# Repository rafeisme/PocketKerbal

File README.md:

# PocketKerbal
Kerbal Space Program Controller using PocketBeagle

(Soon to be) Home to KerbalController!

This is a personalized Kerbal Space Program console built using a PocketBeagle and kRPC. 

More information can be found on my Hackster Page: https://www.hackster.io/rfn1/pocketkerbal-ksp-console-using-pocketbeagle-krpc-d380ad 

The program you need to use/edit is called Project_1_v2
It is actually intiated using a run program. 
For these files, see https://github.com/rafeisme/ENGI301

Currently this repository houses the PCB files for PocketKerbal. These still need some work, but should be functional. The board is the same size as the actual console, and is designed to be fitted behind it. For the sake of simplicity, some of the unique buttons and switches have been temporarily swapped out for generic ones. 
In total there are:
15 toggle switches
4 buttons
20 resistors
2 joysticks
2 potentiometers
2 led bars
2 leds
1 sliding potentiometer
1 display

A more comprehensive parts list can be found on the Hackster Page. 

NOTE: The "PocketBeagle Device" had not been made when the PCB layout was done, so the example PocketBeagle is included here. The file for the custom PocketBeagle is included in the library.
NOTE: The project guidelines mentioned a 4"x5" maximum size, but in order to fit all of the components and be the size of the console, PocketKerbal is 12" x 6". It could be reduced if it was necessary. 
NOTE: The LCD screen was used as opposed to the SPI screen in my library. https://www.adafruit.com/product/181 

This is still a work in progress and will be updated soon.

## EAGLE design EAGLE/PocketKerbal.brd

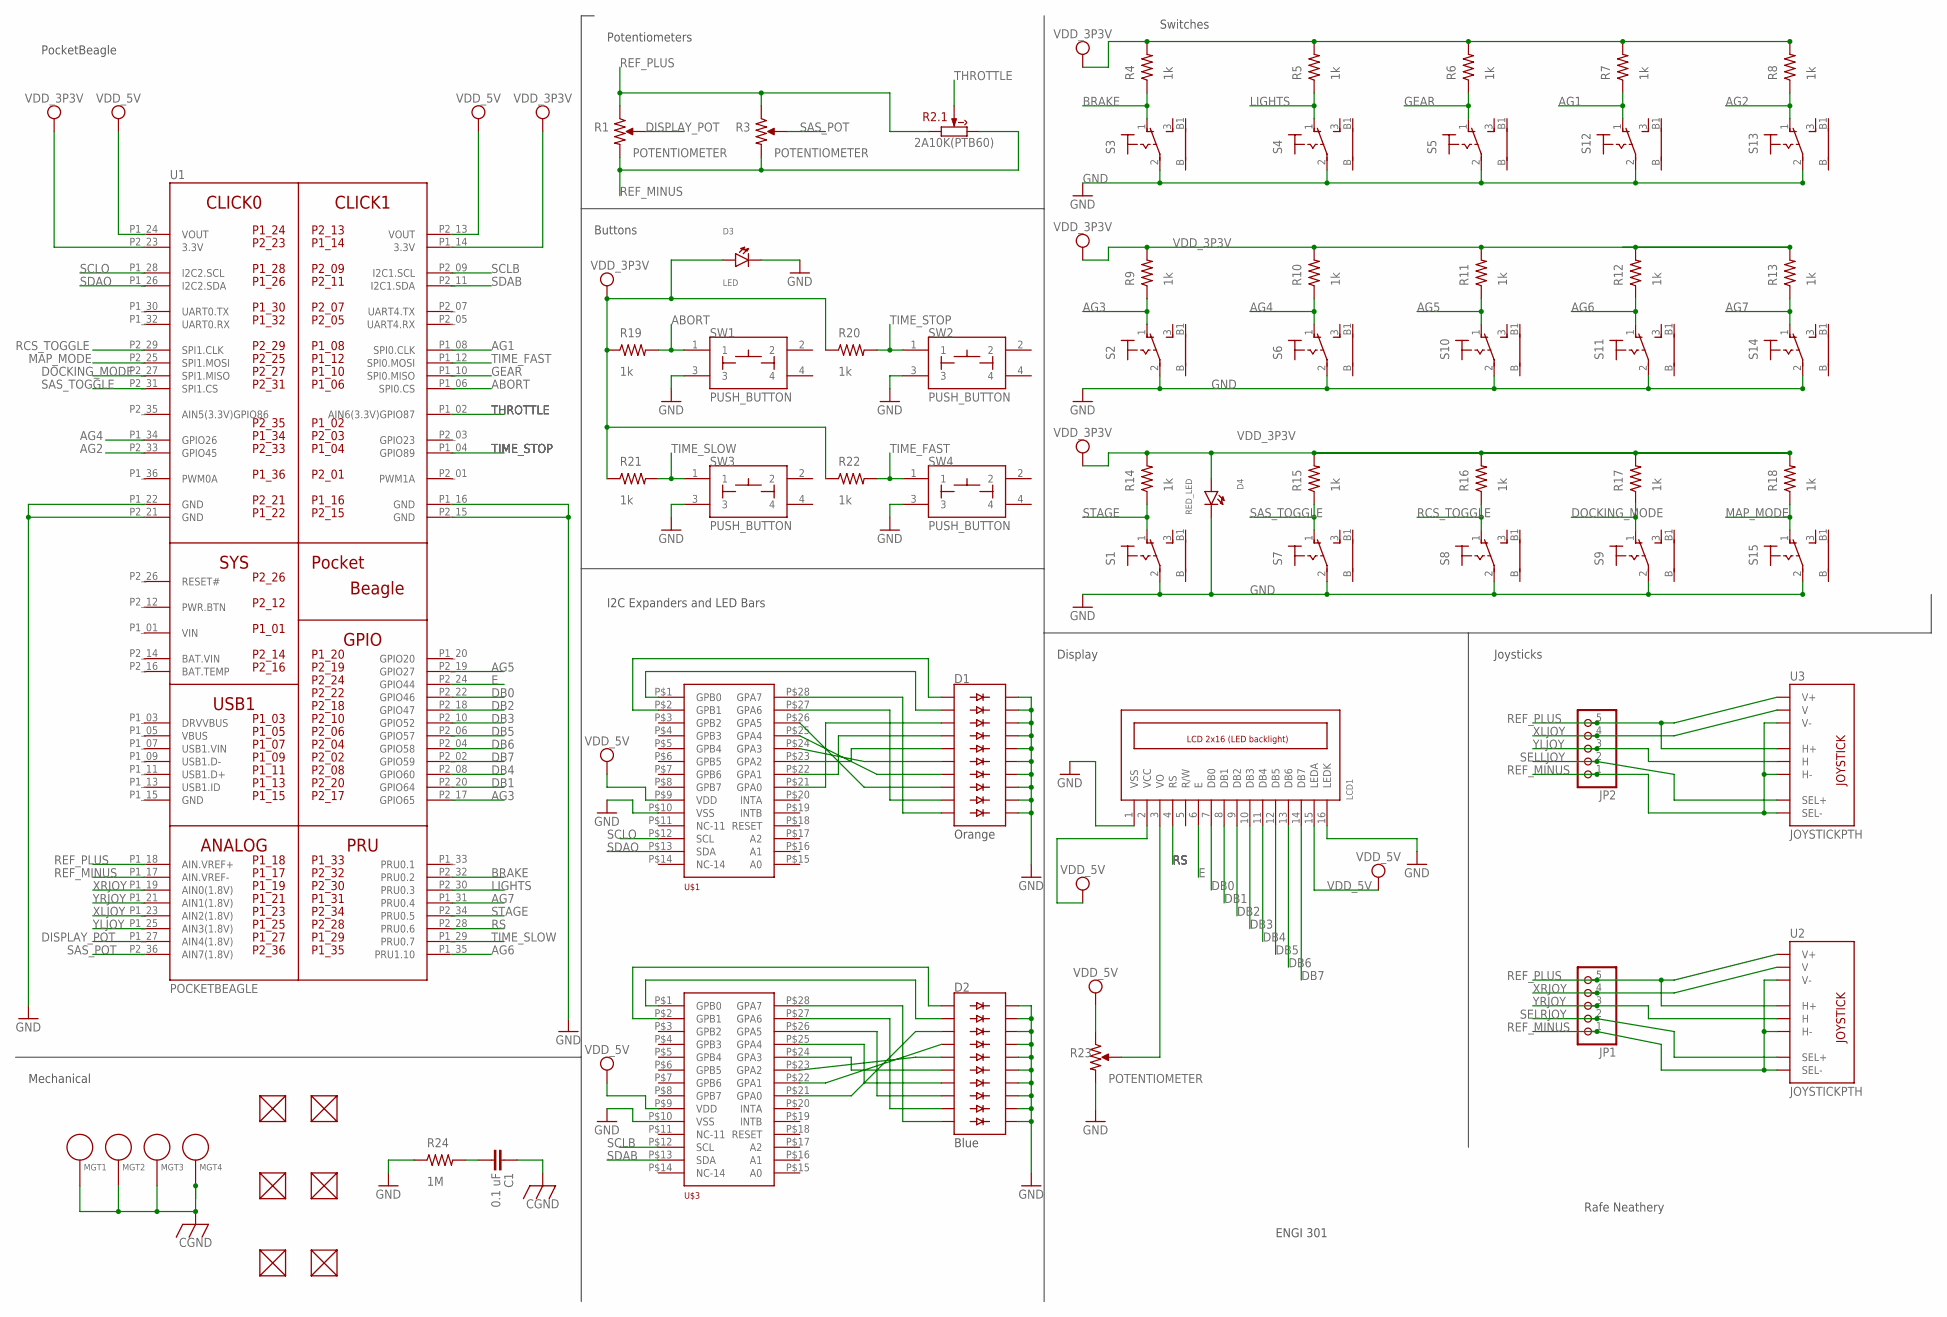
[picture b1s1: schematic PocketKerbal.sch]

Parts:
C1: 0.1 uF; C0402
D1, D2: RED; LED_BARGRAPH_10
D3: LED; EIA-STD
D4: RED_LED; EIA-STD
FUD1, FUD2, FUD5, FUD6, FUD9, FUD10: FIDUCIAL; FIDUCIAL_40MIL
JP1, JP2: PINHD-1X5; 1X05
LCD1: LCD_2X16_SIL; HY-1602F
MGT1, MGT2, MGT3, MGT4: MOUNTING_HOLE
R1, R3, R23: POTENTIOMETER; POT-PO90S
R2: 2A10K(PTB60); PTB6044
R4, R5, R6, R7, R8, R9, R10, R11, R12, R13, R14, R15, R16, R17, R18, R19, R20, R21, R22: 1k; R0603
R24: 1M; R0603
S1, S2, S3, S4, S5, S6, S7, S8, S9, S10, S11, S12, S13, S14, S15: 9070-1W
SW1, SW2, SW3, SW4: PUSH_BUTTON; BUTTON_12.5MM
U1: POCKETBEAGLE
U2, U3: JOYSTICKPTH; JOYSTICK
U$1, U$3: MCP23017-E/SP; DIP28

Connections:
ABORT: R19.2, SW1.1, U1.P1_06 (SPI0.CS)
AG1: R7.1, S12.1 (O), U1.P1_08 (SPI0.CLK)
AG2: R8.1, S13.1 (O), U1.P2_33 (GPIO45)
AG3: R9.1, S2.1 (O), U1.P2_17 (GPIO65)
AG4: R10.1, S6.1 (O), U1.P1_34 (GPIO26)
AG5: R11.1, S10.1 (O), U1.P2_19 (GPIO27)
AG6: R12.1, S11.1 (O), U1.P1_35 (PRU1.10)
AG7: R13.1, S14.1 (O), U1.P1_31 (PRU0.4)
BAT.VIN: U1.P2_14 (BAT.VIN)
BRAKE: R4.1, S3.1 (O), U1.P2_32 (PRU0.2)
CGND: C1.1, MGT1.P$1, MGT2.P$1, MGT3.P$1, MGT4.P$1
DB0: LCD1.7 (DB0), U1.P2_22 (GPIO46)
DB1: LCD1.8 (DB1), U1.P2_20 (GPIO64)
DB2: LCD1.9 (DB2), U1.P2_18 (GPIO47)
DB3: LCD1.10 (DB3), U1.P2_10 (GPIO52)
DB4: LCD1.11 (DB4), U1.P2_08 (GPIO60)
DB5: LCD1.12 (DB5), U1.P2_06 (GPIO57)
DB6: LCD1.13 (DB6), U1.P2_04 (GPIO58)
DB7: LCD1.14 (DB7), U1.P2_02 (GPIO59)
DISPLAY_POT: R1.S, U1.P1_27 (AIN4(1.8V))
DOCKING_MODE: R17.1, S9.1 (O), U1.P2_27 (SPI1.MISO)
E: LCD1.6 (E), U1.P2_24 (GPIO44)
GEAR: R6.1, S5.1 (O), U1.P1_10 (SPI0.MISO)
GND: D1.11 (C9), D1.12 (C8), D1.13 (C7), D1.14 (C6), D1.15 (C5), D1.16 (C4), D1.17 (C3), D1.18 (C2), D1.19 (C1), D1.20 (C), D2.11 (C9), D2.12 (C8), D2.13 (C7), D2.14 (C6), D2.15 (C5), D2.16 (C4), D2.17 (C3), D2.18 (C2), D2.19 (C1), D2.20 (C), D3.CATHODE, D4.CATHODE, LCD1.1 (VSS), LCD1.16 (LEDK), R23.CW, R24.1, S1.2, S2.2, S3.2, S4.2, S5.2, S6.2, S7.2, S8.2, S9.2, S10.2, S11.2, S12.2, S13.2, S14.2, S15.2, SW1.3, SW2.3, SW3.3, SW4.3, U1.P1_16 (GND), U1.P1_22 (GND), U1.P2_15 (GND), U1.P2_21 (GND), U$1.P$10 (VSS), U$3.P$10 (VSS)
LIGHTS: R5.1, S4.1 (O), U1.P2_30 (PRU0.3)
MAP_MODE: R18.1, S15.1 (O), U1.P2_25 (SPI1.MOSI)
unnamed: D2.3 (A2), U$3.P$21 (GPA0)
unnamed: D2.4 (A3), U$3.P$22 (GPA1)
unnamed: D2.10 (A9), U$3.P$28 (GPA7)
unnamed: D2.9 (A8), U$3.P$27 (GPA6)
unnamed: D2.8 (A7), U$3.P$26 (GPA5)
unnamed: D2.7 (A6), U$3.P$25 (GPA4)
unnamed: D2.6 (A5), U$3.P$24 (GPA3)
unnamed: D2.5 (A4), U$3.P$23 (GPA2)
unnamed: D2.2 (A1), U$3.P$1 (GPB0)
unnamed: D1.3 (A2), U$1.P$21 (GPA0)
unnamed: LCD1.3 (VO), R23.S
unnamed: D1.6 (A5), U$1.P$24 (GPA3)
unnamed: D1.7 (A6), U$1.P$25 (GPA4)
unnamed: D1.8 (A7), U$1.P$26 (GPA5)
unnamed: D1.9 (A8), U$1.P$27 (GPA6)
unnamed: D1.10 (A9), U$1.P$28 (GPA7)
unnamed: D1.2 (A1), U$1.P$1 (GPB0)
unnamed: D1.1 (A), U$1.P$2 (GPB1)
unnamed: D2.1 (A), U$3.P$2 (GPB1)
unnamed: C1.2, R24.2
unnamed: D1.5 (A4), U$1.P$23 (GPA2)
unnamed: D1.4 (A3), U$1.P$22 (GPA1)
RCS_TOGGLE: R16.1, S8.1 (O), U1.P2_29 (SPI1.CLK)
REF_MINUS: JP1.1, JP2.1, R1.CW, R2.A3 (CW), R3.CW, U1.P1_17 (AIN.VREF-), U2.B2A (SEL-), U2.H3 (H-), U2.V3 (V-), U3.B2A (SEL-), U3.H3 (H-), U3.V3 (V-)
REF_PLUS: JP1.5, JP2.5, R1.CCW, R2.A1 (CCW), R3.CCW, U1.P1_18 (AIN.VREF+), U2.H1 (H+), U2.V1 (V+), U3.H1 (H+), U3.V1 (V+)
RS: LCD1.4 (RS), U1.P2_28 (PRU0.6)
SAS_POT: R3.S, U1.P2_36 (AIN7(1.8V))
SAS_TOGGLE: R15.1, S7.1 (O), U1.P2_31 (SPI1.CS)
SCLB: U1.P2_09 (I2C1.SCL), U$3.P$12 (SCL)
SCLO: U1.P1_28 (I2C2.SCL), U$1.P$12 (SCL)
SDAB: U1.P2_11 (I2C1.SDA), U$3.P$13 (SDA)
SDAO: U1.P1_26 (I2C2.SDA), U$1.P$13 (SDA)
SELLJOY: JP2.2, U3.B1A (SEL+)
SELRJOY: JP1.2, U2.B1A (SEL+)
STAGE: R14.1, S1.1 (O), U1.P2_34 (PRU0.5)
THROTTLE: R2.A2 (W), U1.P1_02 (AIN6(3.3V)GPIO87)
TIME_FAST: R22.2, SW4.1, U1.P1_12 (SPI0.MOSI)
TIME_SLOW: R21.2, SW3.1, U1.P1_29 (PRU0.7)
TIME_STOP: R20.2, SW2.1, U1.P1_04 (GPIO89)
VDD_3P3V: D3.ANODE, D4.ANODE, R4.2, R5.2, R6.2, R7.2, R8.2, R9.2, R10.2, R11.2, R12.2, R13.2, R14.2, R15.2, R16.2, R17.2, R18.2, R19.1, R20.1, R21.1, R22.1, U1.P1_14 (3.3V), U1.P2_23 (3.3V)
VDD_5V: LCD1.2 (VCC), LCD1.15 (LEDA), R23.CCW, U1.P1_24 (VOUT), U1.P2_13 (VOUT), U$1.P$9 (VDD), U$3.P$9 (VDD)
VIN: U1.P1_01 (VIN)
XLJOY: JP2.4, U1.P1_23 (AIN2(1.8V)), U3.V2 (V)
XRJOY: JP1.4, U1.P1_19 (AIN0(1.8V)), U2.V2 (V)
YLJOY: JP2.3, U1.P1_25 (AIN3(1.8V)), U3.H2 (H)
YRJOY: JP1.3, U1.P1_21 (AIN1(1.8V)), U2.H2 (H)

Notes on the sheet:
PocketBeagle
Potentiometers
Buttons
I2C Expanders and LED Bars
Switches
Joysticks
Display
Blue
Orange
Mechanical
ENGI 301
Rafe Neathery

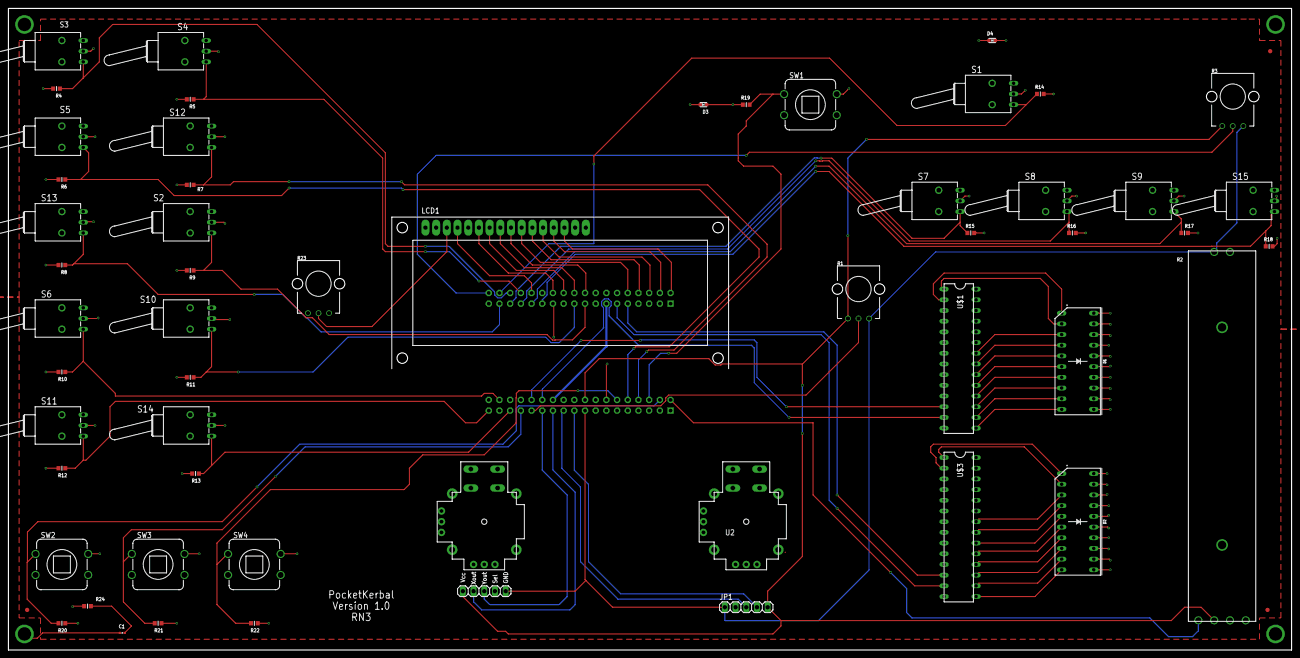
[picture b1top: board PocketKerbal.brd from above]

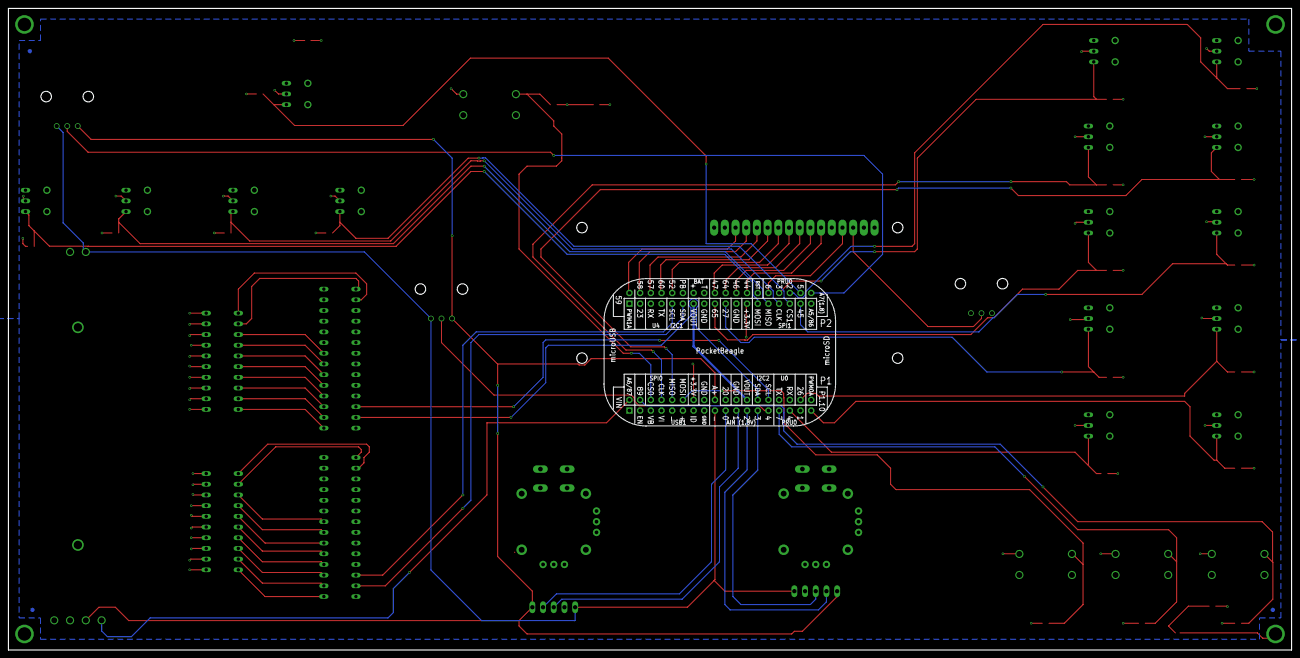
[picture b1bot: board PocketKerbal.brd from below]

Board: 4 copper layers, 304.8 x 152.4 mm, 66 parts (4 on the bottom side), 70 nets.

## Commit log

2023-05-03 PocketKerbal PCB v1
    First version of PocketKerbal PCB files

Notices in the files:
parts and their libraries:
SparkFun-LED: Licensing: Creative Commons ShareAlike 4.0 International - https://creativecommons.org/licenses/by-sa/4.0
